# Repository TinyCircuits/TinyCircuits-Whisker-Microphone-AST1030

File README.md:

# TinyCircuits Wireling Microphone
# AST1030 Rev1

The design files are located under design_files/ for the TinyCircuits AST1030 Rev 1 PCB. This is a Wireling board which features a  miniature, high performance, low power, top port silicon microphone, the SPW2430HR5H-B, that consists of an acoustic sensor, a low noise input buffer, and an output amplifier.  Ideal for portable sound recording of short samples.

Format is in Cadsoft Eagle format - Eagle version 6.2 was used for the original design.

For more infomation on this, check out the product page at TinyCircuits.com

# License:

Design by TinyCircuits.
All design files are released under the Creative Commons Attribution Share-Alike 3.0 License, see the following link for details: http://creativecommons.org/licenses/by-sa/3.0

All text above must be included in any redistribution or derived design

This project uses designs and concepts developed as part of the Arduino project and the LilyPad project.  The TinyCircuits design files themselves (schematics, PCB and libraries) are not directly derived from these works' design files and have been created new, however the concepts and basic architecture behind the TinyDuino and TinyLily products are derived and we thank the hard work of the organizations below for their contributions to open-source hardware:
  
Original Arduino Uno Design by Team Arduino

LilyPad Arduino Design by Leah Buechley and Sparkfun Electronics

Please support the open-source hardware community

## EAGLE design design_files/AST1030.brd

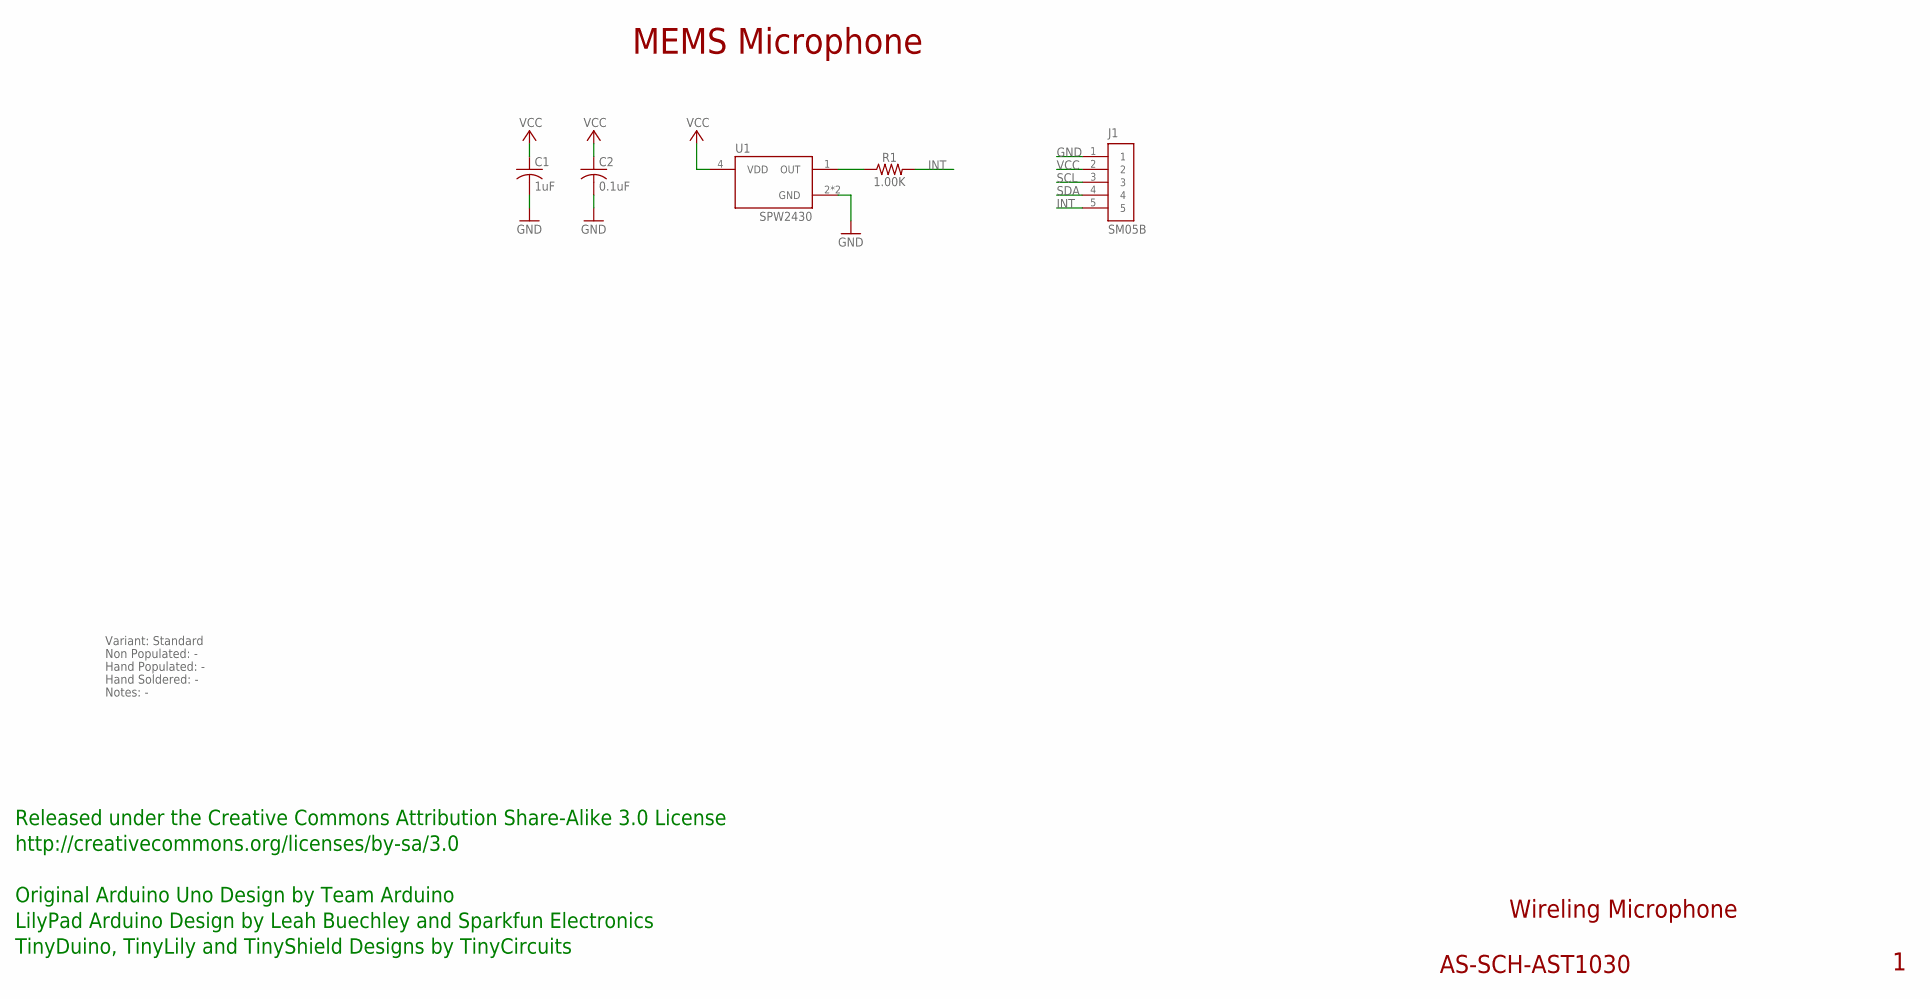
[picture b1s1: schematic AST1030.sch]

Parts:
C1: 1uF; C0603; PARTNO AS-ITM-00410
C2: 0.1uF; C0402
J1: SM05B; JST_SH_5X1_EDGE
R1: 1.00K; 0402
U1: SPW2430; SPW2430HR5H-B

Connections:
GND: C1.2, C2.2, J1.1, U1.2 (GND), U1.3 (GND)
INT: J1.5, R1.2
unnamed: R1.1, U1.1 (OUT)
SCL: J1.3
SDA: J1.4
VCC: C1.1, C2.1, J1.2, U1.4 (VDD)

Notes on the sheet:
Wireling Microphone
AS-SCH-AST1030
MEMS Microphone
Released under the Creative Commons Attribution Share-Alike 3.0 License
http://creativecommons.org/licenses/by-sa/3.0
Original Arduino Uno Design by Team Arduino
TinyDuino, TinyLily and TinyShield Designs by TinyCircuits
LilyPad Arduino Design by Leah Buechley and Sparkfun Electronics
Non Populated: -
Hand Populated: -
Hand Soldered: -
Variant: Standard
Notes: -

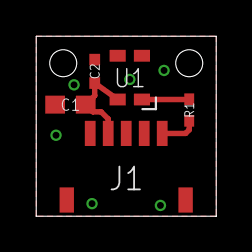
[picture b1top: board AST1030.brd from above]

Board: 2 copper layers, 10.0 x 10.0 mm, 6 parts (0 on the bottom side), 4 nets.

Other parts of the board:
U$1: DOCFIELD-TINYCIRCUITS-PCB

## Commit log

2019-07-16 fixed namin convention
2019-07-17 added images
2019-07-18 changed code to use Port 0
2019-08-05 added datasheet
2019-10-29 name change
2019-12-17 updated documentation
2020-02-04 mass image update
2020-08-14 Add CAD data
